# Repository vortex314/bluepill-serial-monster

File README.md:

# maple-serial-monster

The original project on the blue pill has been cloned, so for the bluepill please use the original github repo.

I added 2 features
- Build easily with the platformio plugin in vscode ( it addresses all pre-requisites )
- Support the  [Maple mini board](https://www.leaflabs.com/maple) 

Since some pins needed to be remapped , it is possible that not all settings are possible. 
As my need was limited to pure transmit/receive this was not an issue.
My firt use case was to control a main hoverboard and 1 or 2 sideboards via a serial protocol. 

# Kicad board

Under the kicad directory you can find the design of a small board with 4 pst connectors : 3 x USART + 1 SWD. 
Most PCB fabs accept the gerber.zip file.

# Doc directory

This contains soem additional documentation on the maple mini board. 

## maple build instructions
- Follow these [instructions ](https://platformio.org/install/ide?install=vscode) and install vscode+platformio for you platform 
- Go to the folder where you downloaded this project
- Press build and download to the maple via stlink. 

# bluepill-serial-monster

_bluepill-serial-monster_ is a firmware for _STM32 Blue Pill_ that turns it
into a _3 Port USB-to-Serial_ adapter. The firmware implements a USB 2.0
full-speed composite device that consists of 3 USB CDC devices.

_STM32 Blue Pill_ is a ridiculously cheap _STM32_ development board which
is available in many stores around the globe. The board contains decent
hardware that supports _USB 2.0 Full-Speed_, has 3 independent _USARTs_
and enough processing power to handle high-speed _UART_ communications.

**Note**: some _Blue Pill_ clones have an incorrect pull-up resistor soldered
to the _USB D+_ line (_PA12_) which prevents them from being successfully
detected by the host. Please refer to
[Fixing USB on Blue Pill Boards](#fixing-usb-on-blue-pill-boards)
for more information.

Some USB controllers work fine even with faulty _Blue Pill_ boards. If your
board works with your computer, don't bother fixing it.

## Features

* 3 independent _UART_ ports;
* Hardware flow control (**RTS**/**CTS**) support<sup>1</sup>;
* **DSR**/**DTR**/**DCD**/**RI** signals support;
* 7 or 8 bit word length;
* None, even, odd parity;
* 1, 1.5, and 2 stop bits;
* Works with _CDC Class_ drives on _Linux_, _macOS_, and _Windows_;
* Supports all baud rates up to 2 MBaud;
* **TXA** signal for controlling RS-485 transceivers (**DE**, **/RE**);
* _DMA_ _RX_/_TX_ for high-speed communications;
* _IDLE line_ detection for short response time;
* Signed _INF_ driver for _Windows XP, 7, and 8_;
* Built-in command shell for device parameters configuration;
* No external dependencies other than _CMSIS_;
* DFU Bootloaders Compartible (see the _FIRMWARE_ORIGIN_ option);

(1) _UART1_ does not support _CTS_ because it is occupied by USB (_PA11_)
and cannot be remapped. _RTS_ can still be used.

## Donations

If this project helped you with whatever you use it for
or you just want to say thanks, you can buy me a coffee :)

## UART Signal Levels

Although _STM32F103C8T6_ installed on the Blue Pill board is a **3.3 V**
device, a number of its inputs are actually **5 V** tolerant.
This means you can safely use the selected inputs with **3.3** and **5 V**
TTL devices.

**Do not use non 5 V tolerant inputs with 5 V devices as doing that will
result in permanent damage of MCU inputs or MCU itself.**

**When configured as an output, none of the _STM32F103C8T6_ pins is 5 V
tolerant. Make sure you don't accidentally get more than 4.0 V on such pin
or damage may occur.**

**5 V** tolerant pins are shown **in bold** in the next section.

## UART Pinout

| Signal |   Direction   |     UART1     |     UART2     |     UART3     |
|:-------|:-------------:|:--------------|:--------------|:--------------|
|   RX   |      IN       |    **PA10**   |      PA3      |    **PB11**   |
|   TX   |      OUT      |      PA9      |      PA2      |      PB10     |
|   RTS  |      OUT      |    **PA15**   |      PA1      |      PB14     |
|   CTS  |      IN       |      N/A      |      PA0      |    **PB13**   |
|   DSR  |      IN       |    **PB7**    |    **PB4**    |    **PB6**    |
|   DTR  |      OUT      |      PA4      |      PA5      |      PA6      |
|   DCD  |      IN       |    **PB15**   |    **PB8**    |    **PB9**    |
|   RI   |      IN       |    **PB3**    |    **PB12**   |    **PA8**    |
|   TXA  |      OUT      |    **PB0**    |    **PB1**    |    **PA7**    |

Note: **5 V** tolerant input pins are shown **in bold**.

## Control Signals (Default Configuration)

**RTS**, **CTS**, **DSR**, **DTR**, **DCD**, **RI** are **active-low** signals,
**TXA** is an active-high signal.

**TXA** (**TX** **A**ctive) is active when UART is transmitting data and
can be used to control **DE** and **/RE** pins of RS-485 transceivers.

**TXA** goes inactive within 0.6 us after the transmission is complete,
which meets RS-485 and IO-link timing requirements at speeds up to 920 kBaud
with almost double safety margin.

**DSR**, **DTR**, and **DCD**, **RI** are connected to the internal _weak pull-up_
resistors, so they remain inactive at rest.

**CTS** is **pulled down** internally, which enables _UART TX_ when nothing is
connected to **CTS**. Hardware flow control is always on, but it does not get
in the way of communications as long as nothing is connected to the flow control lines.

**RTS** can be controlled by the host, but as soon as the _UART RX_ buffer is
**half-full**, **RTS** is forced to the **inactive** state. As long as more than
one half of the buffer space is available, **RTS** remains in the state set
by the host. Please take this behaviour into account if you rely on the
**RTS** signal to control non-standard periphery.

**DSR**, **DCD**, and **RI** are polled 50 times per second.

_UART DMA RX/TX_ buffer size is **1024** bytes.

## Mapping Logical Port Names to Physical Ports

Unfortunately, operating systems ignore CDC port names reported by the firmware.
_Linux_ and _macOS_ tend to assign device numbers incrementally so that UART1 gets
the lowest and UART3 the highest **/dev/ttyACM...** (_Linux_) or
**/dev/tty.usbmodem...** (_macOS_) numbers. On the other hand, _Windows_ can get
pretty creative when assigning COM port numbers to USB CDC devices.

To find out which physical UART corresponds to a particular COM port on _Windows_,
open **Device Manager**, right click on the COM port under **Ports (COM & LPT)**,
and choose **Properties**. Open the **Details** tab and select
the **Bus reported device description** property.
The **Value** field will indicate the physical UART name.

## Windows Usbser.sys RTS Bug

All versions of _Windows_ have a bug in the USB CDC system driver (**usbser.sys**)
that affects RTS signal handling.

The driver does not send USB **SET_CONTROL_LINE_STATE** messages when
the **RTS** state changes. However, on the **DTR** state change, the driver sends
a **SET_CONTROL_LINE_STATE** message containing the updated states for both
**RTS** and **DTR** signals.

It is unknown why **usbser.sys** does this, but the disassembled code
of the driver suggests that sending **SET_CONTROL_LINE_STATE** on **RTS** change
is simply left out by mistake. It looks like _Microsoft_ is not going to fix
this bug. However, it can be easily worked around.

The workaround for this bug is to update DTR (even to the same state) each time
RTS needs to be updated as in the example below:

```c
#include <windows.h>
#include <stdio.h>

int main() {
    HANDLE hComm = CreateFileA("\\\\.\\COM5", GENERIC_READ | GENERIC_WRITE,
        0, NULL, OPEN_EXISTING, 0, NULL);
    if (hComm == INVALID_HANDLE_VALUE) {
        printf("Error opening serial port\n");
    } else {
        printf("Serial port opened\n");
    }
    while (1) {
        // I don't know any easy (and reliable) way to get current DTR state in WinAPI unfortunately.
        // Probably the simplest solution is to keep current DTR value in a variable.
        EscapeCommFunction(hComm, SETRTS);
        EscapeCommFunction(hComm, CLRDTR); // or SETDTR, does not matter
        (void)getc(stdin);
        EscapeCommFunction(hComm, CLRRTS);
        EscapeCommFunction(hComm, CLRDTR); // or SETDTR, does not matter
        (void)getc(stdin);
    }
    CloseHandle(hComm);
    return 0;
}
```

Some existing software already does that. _CwType_, _Win-Test_, _CoolTerm_
are the examples of such software. Others like _N1MM Logger Plus_ or _Termite_
do not implement the workaround.

The RTS issue does not affect _Linux_ or _macOS_.

## Unexpected Echo or Garbage Characters in Linux

_Linux_ terminal subsystem echoes characters coming from a
_bluepill-serial-monster_ port back to this port until it is switched to
the raw more (see ```man 3 cfmakeraw```).

This behaviour is Linux-specific and is not related to
_bluepill-serial-monster_ itself. See
[this Stack Overflow post](https://stackoverflow.com/questions/14866899/linux-cdc-acm-device-unexpected-characters-sent-to-device)
for details.

Usually, this is not an issue; however, it may lead to garbage characters
appearing when the configuration shell is started. For instance, if **PA5**
is tied to the ground when _bluepill-serial-monster_ is plugged in, the device
sends the configuration mode banner to the host. The host echoes the content of
the banner back to the device, which in turn tries to parse it as if it was
a sequence of configuration shell commands. When _screen_ or another terminal
emulation software is started, its output may contain garbage characters left
due to the above exchange.

## Advanced Configuration

_bluepill-serial-monster_ provides a configuration shell that allows
controlling various parameters of the UART signal lines.

To access the configuration shell, open the first USB serial port (UART1)
with any terminal emulator application (such as _screen_, _Tera Term_, etc.)
and connect **PB5** to ground. Serial port settings do not matter.

You should see the configuration shell prompt:

```text
*******************************
* Configuration Shell Started *
*******************************

>
```

The configuration shell has minimal support for ANSI escape sequences. You can
use the arrow keys to move the cursor when editing a command, erase text with _Backspace_,
and insert text anywhere in the command. You can also recall the last command
by pressing _UP_.

Command and parameter names are case-sensitive.

To get the list of available commands, type:

```text
>help
```

To get command-specific help, type:

```text
>help command-name
```

### UART Port Parameters

UART port parameters can be viewed and set with the _uart_ command:

```text
>help uart
uart: set and view UART parameters
Usage: uart port-number|all show|signal-name-1 param-1 value-1 ... [param-n value-n] [signal-name-2 ...]
Use "uart port-number|all show" to view current UART configuration.
Use "uart port-number|all signal-name-1 param-1 value-1 ... [param-n value-n] [signal-name-2 ...]"
to set UART parameters, where signal names are rx, tx, rts, cts, dsr, dtr, dcd,
and params are:
  output        [pp|od]
  active        [low|high]
  pull          [floating|up|down]
Example: "uart 1 tx output od" sets UART1 TX output type to open-drain
Example: "uart 3 rts active high dcd active high pull down" allows to set multiple parameters at once.
```

Changes to the UART parameters are applied instantly; however, the configuration
is not stored in the flash memory until you explicitly save it with:

```text
>config save
```

To view current configuration of all UART ports, type:

```text
>uart all show
```

To view current configuration of a particular UART port, type:

```text
>uart port-number show
```

where _port-number_ is in range of 1 to 3.

Output type can be set for any output signal. Available output types are:

* **pp** for push-pull output;
* **od** for open-drain output;

Example:

```text
uart 1 tx output od
```

Pull type can be set for any input signal. Available pull types are:

* **floating** for floating input;
* **up** for weak pull up;
* **down** for weak pull down;

Example:

```text
uart 1 dcd pull up
```

Signal polarity can be set for all input and output signals except for **RX**,
**TX**, and **CTS**. Available signal polarities are:

* **low** for active-low signal polarity;
* **high** for active-high signal polarity;

Example:

```text
uart 1 rts active high
```

It is possible to set multiple signal parameters for multiple signals in one
command:

```text
uart 1 tx output od rts output od active high
```

If the uart command encounters a syntax error or an invalid parameter in
the middle of a multiple parameters command line, it stops execution
immediately. However, it does not roll back valid parameters set before
the point where the error occured.

It is also possible to set signal parameters for multiple ports in one command:

```text
uart all tx output od
```

### Saving and Resetting Configuration

To permanently save current device configuration, type:

```text
config save
```

To reset the device to the default settings, type:

```text
config reset
```

### Printing the Firmware Version

To print the firmware version, type:

```text
version
```

The default configuration is automatically stored in the flash memory after reset.

## Flashing Firmware

Download binary firmware from the
[Releases](https://github.com/r2axz/bluepill-serial-monster/releases) page.

Flash with [ST-LINK](https://www.st.com/en/development-tools/st-link-v2.html)
or similar programmer.

```bash
st-flash --format ihex write bluepill-serial-monster.hex
```

It is also possible to flash _STM32F103C8T6_ via a built-in serial bootloader. Visit
[https://www.st.com/en/development-tools/flasher-stm32.html](https://www.st.com/en/development-tools/flasher-stm32.html)
for instructions and software.

You can also use _bluepill-serial-monster-stm32duino-0x8002000.bin_ or _bluepill-serial-monster-stm32duino-0x8005000.bin_ with [STM32duino-bootloader](https://github.com/rogerclarkmelbourne/STM32duino-bootloader) and [dfu-util](http://dfu-util.sourceforge.net).

## Windows Driver (WinXP, 7, 8)

_Windows_ versions prior to _Windows 10_ require an _INF_ file that maps
the device Vendor ID / Product ID to the Microsoft _usbser.sys_ CDC ACM driver.
_Windows 10_ does not require this and loads the standard driver automatically.

A signed _INF_ file for _Windows XP, 7, and 8_ is included in the distribution.
To install the _INF_ file, plug in _bluepill-serial-monster_ and point _Windows_
to a directory containing both **bluepill-serial-monster.inf** and
**bluepill-serial-monster.cat** files during a new device installation.

Alternatively, you can open _Windows Device Manager_, right-click on any of the
_Bluepill Serial Monster_ devices, choose _Update driver_ and point Windows to
the _INF_ file directory from there.

## Fixing USB on Blue Pill Boards

_STM32 Blue Pill_ boards come in slightly different variations. Nevertheless,
their schematic is very similar. Below you will find the instructions on how to
identify and replace the incorrect USB pull-up resistor on any _Blue Pill_ board.

With a digital multimeter, measure resistance between **PA12** and **3.3 V**
pads on the board. If the resistance reads close to **1.5k** (**1500 ohms**),
then your board is either non-faulty or faulty for some other reason,
and this section does not apply.

If the resistance if far away from **1.5k** (such as **4.7k** or **10k**),
you will have to locate the incorrect resistor on the board and replace it
with a **1.5k** or **1.8k** resistor.

If your board has component names on it, locate **R10**. Otherwise, trace the
board to find the incorrect resistor.

Once you identified the incorrect resistor, replace it with a **1.5k** or
**1.8k** resistor.

## Building Firmware

### Prerequisites

Install the following software:

* [GNU make](https://www.gnu.org/software/make/)
* [arm-none-eabi toolchain](
    https://developer.arm.com/tools-and-software/open-source-software/developer-tools/gnu-toolchain/gnu-rm/downloads)
* [open source st-link](<https://github.com/texane/stlink>)
* [STM32CubeF1](
    <https://www.st.com/en/embedded-software/stm32cubef1.html>)

Here is an example assuming everything is installed in ~/stm32/,
and we use _bash_:

ARM toolchain and st-link must be added to PATH.

```bash
# add ARM toolchain path
export PATH=~/stm32/gcc-arm-none-eabi/bin:$PATH
# add stlink path
export PATH=~/stm32/stlink-install/bin:$PATH
```

Path to STM32CubeF1 should be also exported (use ~/.bash_profile):

```bash
# export STM32Cube
export STM32CUBE_PATH=~/stm32/stm32cube
```

## Building

To build the firmware, **cd** to the project directory and run

```bash
make
```

To flash the MCU using st-link, run

```bash
make flash
```

To remove object and dependency files, run

```bash
make clean
```

To remove object, dependency, and firmware files, run

```bash
make distclean
```

### Building for DFU Bootloaders

_DFU_ bootloaders generally require the firmware origin to be relocated
to a higher flash address to allow room for the bootloader itself.
The bootloader documentation should specify the firmware upload address.
By default, _bluepill-serial-monster_ firmware starts at flash origin (0x8000000).
To move the firmware to a custom address, use the **FIRMWARE_ORIGIN** Makefile variable:

```bash
make clean && make FIRMWARE_ORIGIN=0xXXXXXXXX
```

where 0xXXXXXXXX is the required firmware start address.

The firmware release package already includes two prebuilt binaries for use with
[STM32duino-bootloader](https://github.com/rogerclarkmelbourne/STM32duino-bootloader).

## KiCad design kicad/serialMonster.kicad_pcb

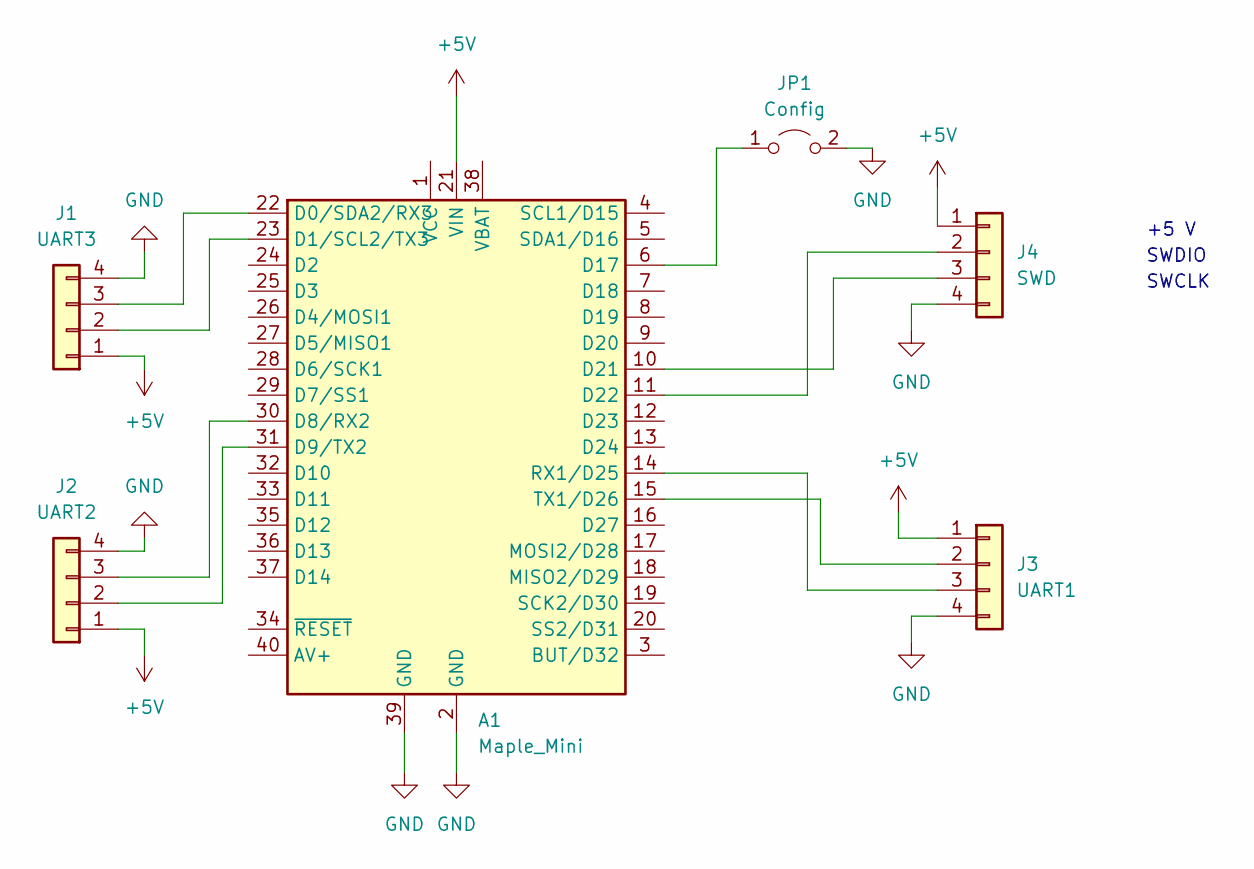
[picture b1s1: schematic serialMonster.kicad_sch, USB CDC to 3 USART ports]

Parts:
A1: Maple_Mini
J1: UART3; JST_XH_S4B-XH-A_1x04_P2.50mm_Horizontal
J2: UART2; JST_XH_S4B-XH-A_1x04_P2.50mm_Horizontal
J3: UART1; JST_XH_S4B-XH-A_1x04_P2.50mm_Horizontal
J4: SWD; JST_XH_S4B-XH-A_1x04_P2.50mm_Horizontal
JP1: Config; TestPoint_2Pads_Pitch2.54mm_Drill0.8mm

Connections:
+5V: A1.21 (VIN), J1.1, J2.1, J3.1, J4.1
GND: A1.2 (GND), A1.39 (GND), J1.4, J2.4, J3.4, J4.4, JP1.2 (B)
unnamed: A1.6 (D17), JP1.1 (A)
unnamed: A1.10 (D21), J4.3
unnamed: A1.11 (D22), J4.2
unnamed: A1.14 (RX1/D25), J3.3
unnamed: A1.15 (TX1/D26), J3.2
unnamed: A1.22 (D0/SDA2/RX3), J1.3
unnamed: A1.23 (D1/SCL2/TX3), J1.2
unnamed: A1.30 (D8/RX2), J2.3
unnamed: A1.31 (D9/TX2), J2.2

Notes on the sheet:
SWDIO
SWCLK
+5 V

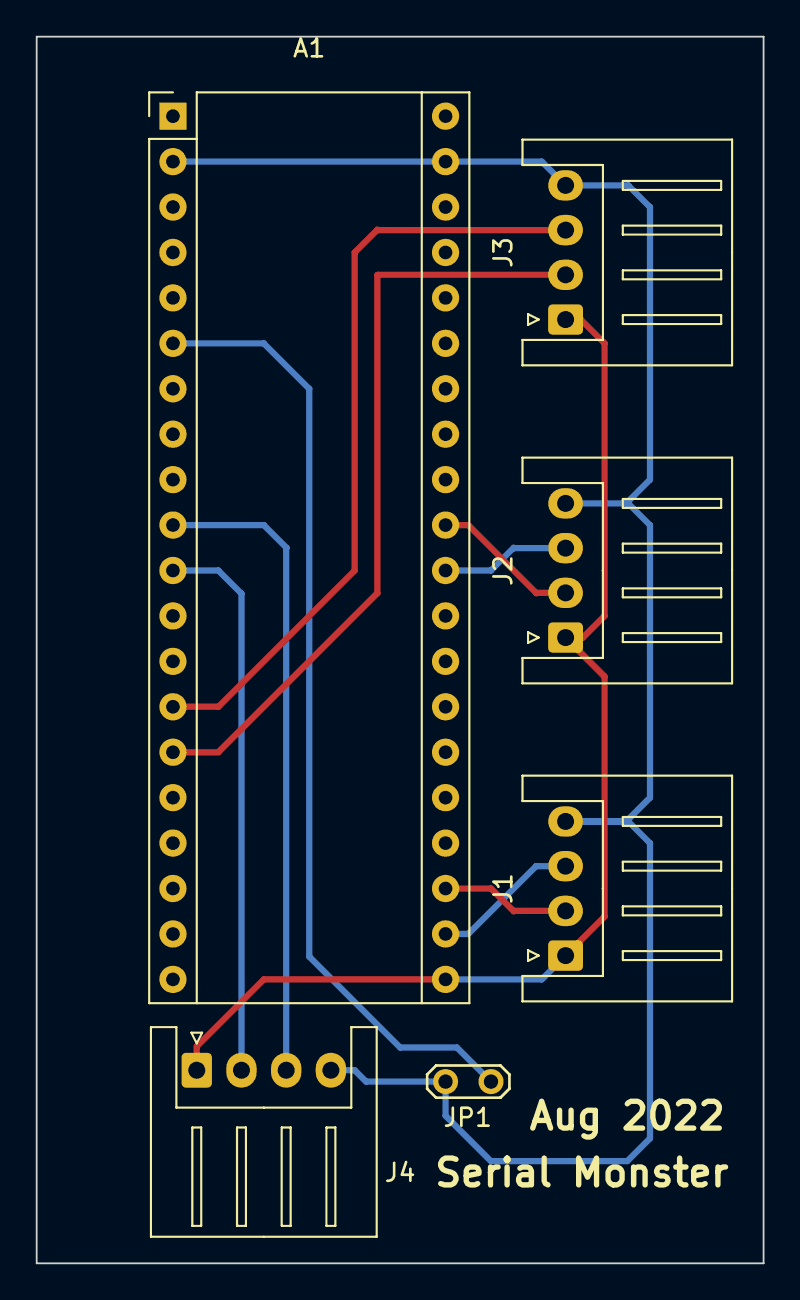
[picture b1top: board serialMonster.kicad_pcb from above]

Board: 2 copper layers, 40.6 x 68.6 mm, 6 parts (0 on the bottom side), 11 nets.

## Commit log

2022-08-22 Adapted code and config for supporting maple mini, also build&debug with platformio and vsbuid
2022-08-22 clean main
2022-08-26 update doc
2022-08-26 corrected doc
2022-08-28 kicad and docs, corrected also txa bug by configuring a dummy txa
2022-08-28 after kicad save :-(
2022-08-28 connector layout
2022-08-28 completing

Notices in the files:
kicad/serialMonster.kicad_pcb:
creativecommons.org/licenses/by/4.0
